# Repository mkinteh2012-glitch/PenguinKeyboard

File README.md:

# PenguinKeyboard
This is a 84 key keyboard built by @penguinmo   
Extra features on this keyboard are none! there isn't any :)  
I built this because i liked making a macropad and it's the samething as a keyboard!

## PICTURES

NOTE: for the Keyboard there is no source CAD because it is exported from kicad

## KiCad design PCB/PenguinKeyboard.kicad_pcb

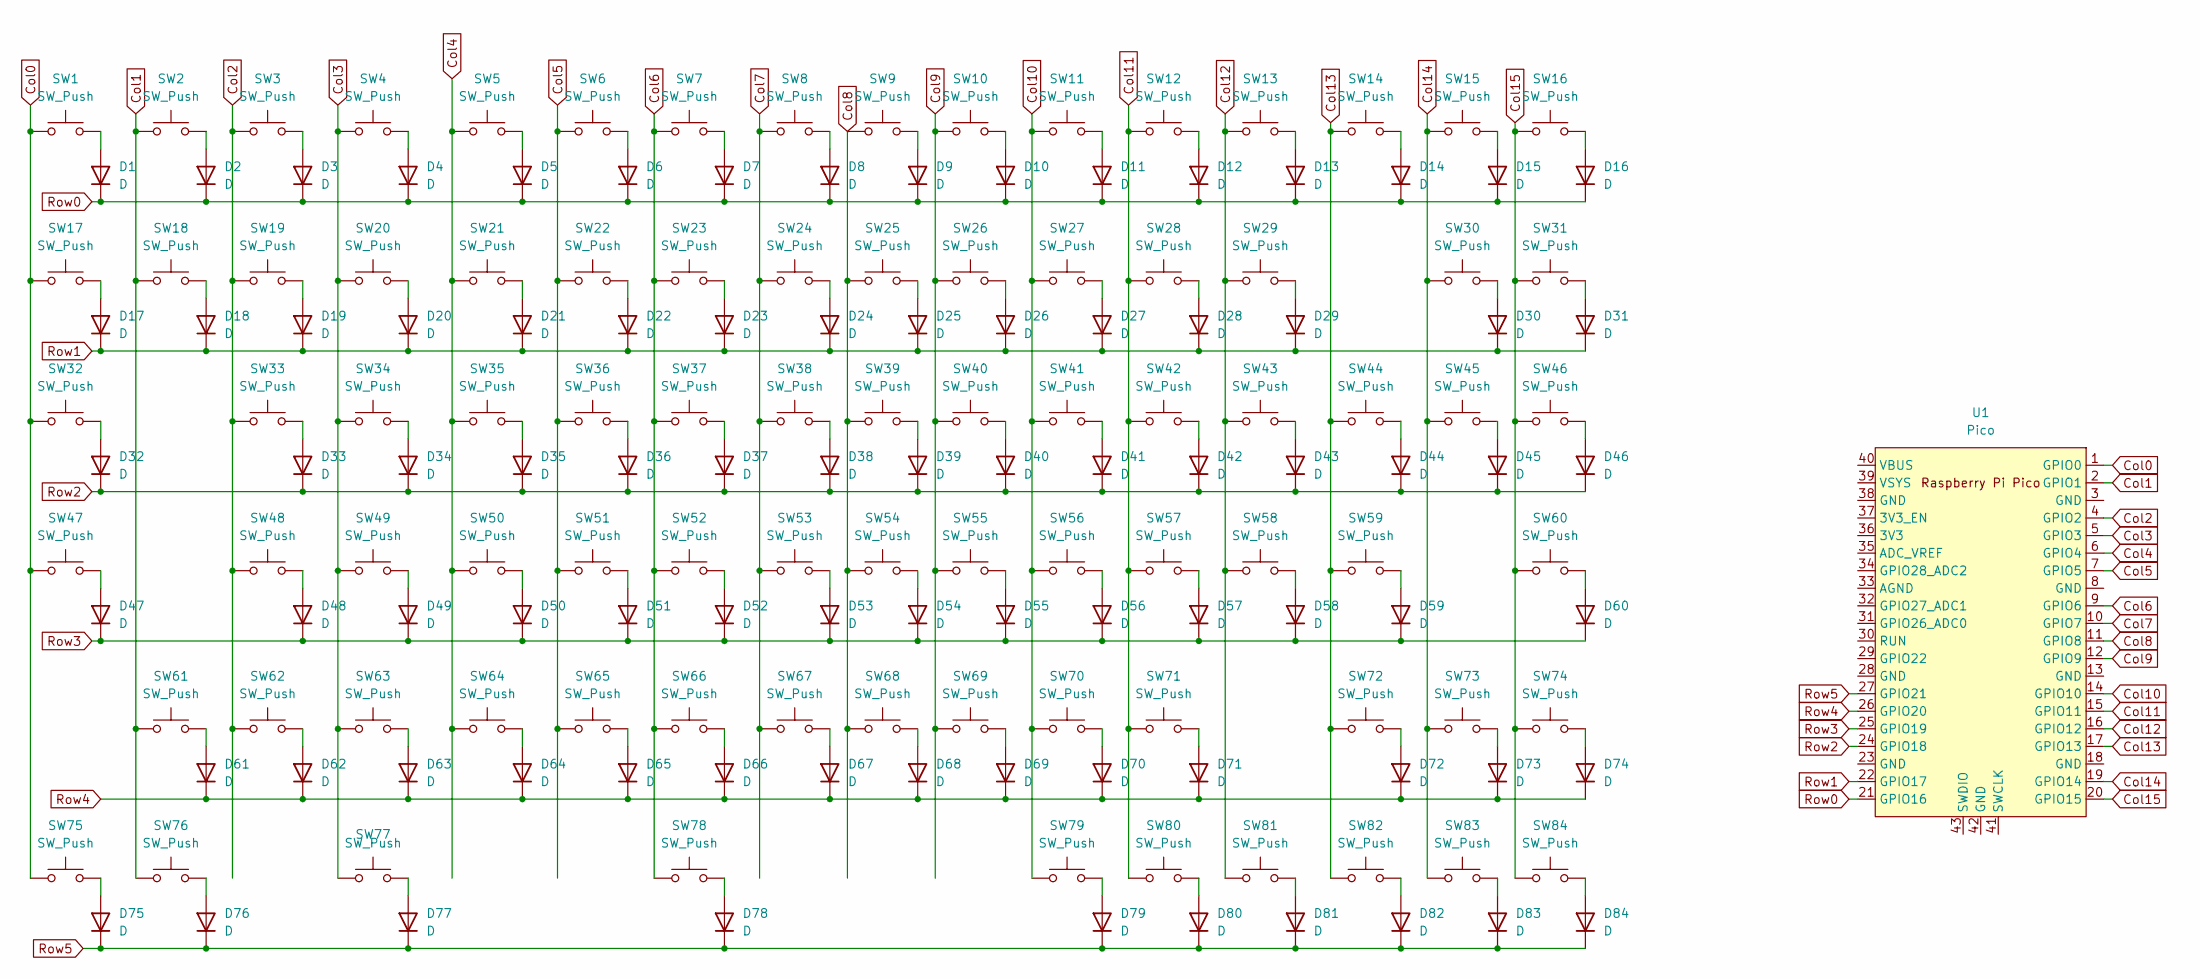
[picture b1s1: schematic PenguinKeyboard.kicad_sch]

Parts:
D1, D2, D3, D4, D5, D6, D7, D8, D9, D10, D11, D12, D13, D14, D15, D16, D17, D18, D19, D20, D21, D22, D23, D24, D25, D26, D27, D28, D29, D30, D31, D32, D33, D34, D35, D36, D37, D38, D39, D40, D41, D42, D43, D44, D45, D46, D47, D48, D49, D50, D51, D52, D53, D54, D55, D56, D57, D58, D59, D60, D61, D62, D63, D64, D65, D66, D67, D68, D69, D70, D71, D72, D73, D74, D75, D76, D77, D78, D79, D80, D81, D82, D83, D84: D; D_DO-35_SOD27_P7.62mm_Horizontal
SW1, SW2, SW3, SW4, SW5, SW6, SW7, SW8, SW9, SW10, SW11, SW12, SW13, SW14, SW15, SW16, SW17, SW18, SW19, SW20, SW21, SW22, SW23, SW24, SW25, SW26, SW27, SW28, SW29, SW30, SW31, SW32, SW33, SW34, SW35, SW36, SW37, SW38, SW39, SW40, SW41, SW42, SW43, SW44, SW45, SW46, SW47, SW48, SW49, SW50, SW51, SW52, SW53, SW54, SW55, SW56, SW57, SW58, SW59, SW60, SW61, SW62, SW63, SW64, SW65, SW66, SW67, SW68, SW69, SW70, SW71, SW72, SW73, SW74, SW75, SW76, SW77, SW78, SW79, SW80, SW81, SW82, SW83, SW84: SW_Push; SW_Cherry_MX_1.00u_PCB
U1: Pico; RPi_Pico_SMD_TH

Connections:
Col0: SW1.1, SW17.1, SW32.1, SW47.1, SW75.1, U1.1 (GPIO0)
Col1: SW2.1, SW18.1, SW61.1, SW76.1, U1.2 (GPIO1)
Col2: SW3.1, SW19.1, SW33.1, SW48.1, SW62.1, U1.4 (GPIO2)
Col3: SW4.1, SW20.1, SW34.1, SW49.1, SW63.1, SW77.1, U1.5 (GPIO3)
Col4: SW5.1, SW21.1, SW35.1, SW50.1, SW64.1, U1.6 (GPIO4)
Col5: SW6.1, SW22.1, SW36.1, SW51.1, SW65.1, U1.7 (GPIO5)
Col6: SW7.1, SW23.1, SW37.1, SW52.1, SW66.1, SW78.1, U1.9 (GPIO6)
Col7: SW8.1, SW24.1, SW38.1, SW53.1, SW67.1, U1.10 (GPIO7)
Col8: SW9.1, SW25.1, SW39.1, SW54.1, SW68.1, U1.11 (GPIO8)
Col9: SW10.1, SW26.1, SW40.1, SW55.1, SW69.1, U1.12 (GPIO9)
Col10: SW11.1, SW27.1, SW41.1, SW56.1, SW70.1, SW79.1, U1.14 (GPIO10)
Col11: SW12.1, SW28.1, SW42.1, SW57.1, SW71.1, SW80.1, U1.15 (GPIO11)
Col12: SW13.1, SW29.1, SW43.1, SW58.1, SW81.1, U1.16 (GPIO12)
Col13: SW14.1, SW44.1, SW59.1, SW72.1, SW82.1, U1.17 (GPIO13)
Col14: SW15.1, SW30.1, SW45.1, SW73.1, SW83.1, U1.19 (GPIO14)
Col15: SW16.1, SW31.1, SW46.1, SW60.1, SW74.1, SW84.1, U1.20 (GPIO15)
unnamed: D1.2 (A), SW1.2
unnamed: D2.2 (A), SW2.2
unnamed: D3.2 (A), SW3.2
unnamed: D4.2 (A), SW4.2
unnamed: D5.2 (A), SW5.2
unnamed: D6.2 (A), SW6.2
unnamed: D7.2 (A), SW7.2
unnamed: D8.2 (A), SW8.2
unnamed: D9.2 (A), SW9.2
unnamed: D10.2 (A), SW10.2
unnamed: D11.2 (A), SW11.2
unnamed: D12.2 (A), SW12.2
unnamed: D13.2 (A), SW13.2
unnamed: D14.2 (A), SW14.2
unnamed: D15.2 (A), SW15.2
unnamed: D16.2 (A), SW16.2
unnamed: D17.2 (A), SW17.2
unnamed: D18.2 (A), SW18.2
unnamed: D19.2 (A), SW19.2
unnamed: D20.2 (A), SW20.2
unnamed: D21.2 (A), SW21.2
unnamed: D22.2 (A), SW22.2
unnamed: D23.2 (A), SW23.2
unnamed: D24.2 (A), SW24.2
unnamed: D25.2 (A), SW25.2
unnamed: D26.2 (A), SW26.2
unnamed: D27.2 (A), SW27.2
unnamed: D28.2 (A), SW28.2
unnamed: D29.2 (A), SW29.2
unnamed: D30.2 (A), SW30.2
unnamed: D31.2 (A), SW31.2
unnamed: D32.2 (A), SW32.2
unnamed: D33.2 (A), SW33.2
unnamed: D34.2 (A), SW34.2
unnamed: D35.2 (A), SW35.2
unnamed: D36.2 (A), SW36.2
unnamed: D37.2 (A), SW37.2
unnamed: D38.2 (A), SW38.2
unnamed: D39.2 (A), SW39.2
unnamed: D40.2 (A), SW40.2
unnamed: D41.2 (A), SW41.2
unnamed: D42.2 (A), SW42.2
unnamed: D43.2 (A), SW43.2
unnamed: D44.2 (A), SW44.2
unnamed: D45.2 (A), SW45.2
unnamed: D46.2 (A), SW46.2
unnamed: D47.2 (A), SW47.2
unnamed: D48.2 (A), SW48.2
unnamed: D49.2 (A), SW49.2
unnamed: D50.2 (A), SW50.2
unnamed: D51.2 (A), SW51.2
unnamed: D52.2 (A), SW52.2
unnamed: D53.2 (A), SW53.2
unnamed: D54.2 (A), SW54.2
unnamed: D55.2 (A), SW55.2
unnamed: D56.2 (A), SW56.2
unnamed: D57.2 (A), SW57.2
unnamed: D58.2 (A), SW58.2
unnamed: D59.2 (A), SW59.2
unnamed: D60.2 (A), SW60.2
unnamed: D61.2 (A), SW61.2
unnamed: D62.2 (A), SW62.2
unnamed: D63.2 (A), SW63.2
unnamed: D64.2 (A), SW64.2
unnamed: D65.2 (A), SW65.2
unnamed: D66.2 (A), SW66.2
unnamed: D67.2 (A), SW67.2
unnamed: D68.2 (A), SW68.2
unnamed: D69.2 (A), SW69.2
unnamed: D70.2 (A), SW70.2
unnamed: D71.2 (A), SW71.2
unnamed: D72.2 (A), SW72.2
unnamed: D73.2 (A), SW73.2
unnamed: D74.2 (A), SW74.2
unnamed: D75.2 (A), SW75.2
unnamed: D76.2 (A), SW76.2
unnamed: D77.2 (A), SW77.2
unnamed: D78.2 (A), SW78.2
unnamed: D79.2 (A), SW79.2
unnamed: D80.2 (A), SW80.2
unnamed: D81.2 (A), SW81.2
unnamed: D82.2 (A), SW82.2
unnamed: D83.2 (A), SW83.2
unnamed: D84.2 (A), SW84.2
Row0: D1.1 (K), D2.1 (K), D3.1 (K), D4.1 (K), D5.1 (K), D6.1 (K), D7.1 (K), D8.1 (K), D9.1 (K), D10.1 (K), D11.1 (K), D12.1 (K), D13.1 (K), D14.1 (K), D15.1 (K), D16.1 (K), U1.21 (GPIO16)
Row1: D17.1 (K), D18.1 (K), D19.1 (K), D20.1 (K), D21.1 (K), D22.1 (K), D23.1 (K), D24.1 (K), D25.1 (K), D26.1 (K), D27.1 (K), D28.1 (K), D29.1 (K), D30.1 (K), D31.1 (K), U1.22 (GPIO17)
Row2: D32.1 (K), D33.1 (K), D34.1 (K), D35.1 (K), D36.1 (K), D37.1 (K), D38.1 (K), D39.1 (K), D40.1 (K), D41.1 (K), D42.1 (K), D43.1 (K), D44.1 (K), D45.1 (K), D46.1 (K), U1.24 (GPIO18)
Row3: D47.1 (K), D48.1 (K), D49.1 (K), D50.1 (K), D51.1 (K), D52.1 (K), D53.1 (K), D54.1 (K), D55.1 (K), D56.1 (K), D57.1 (K), D58.1 (K), D59.1 (K), D60.1 (K), U1.25 (GPIO19)
Row4: D61.1 (K), D62.1 (K), D63.1 (K), D64.1 (K), D65.1 (K), D66.1 (K), D67.1 (K), D68.1 (K), D69.1 (K), D70.1 (K), D71.1 (K), D72.1 (K), D73.1 (K), D74.1 (K), U1.26 (GPIO20)
Row5: D75.1 (K), D76.1 (K), D77.1 (K), D78.1 (K), D79.1 (K), D80.1 (K), D81.1 (K), D82.1 (K), D83.1 (K), D84.1 (K), U1.27 (GPIO21)

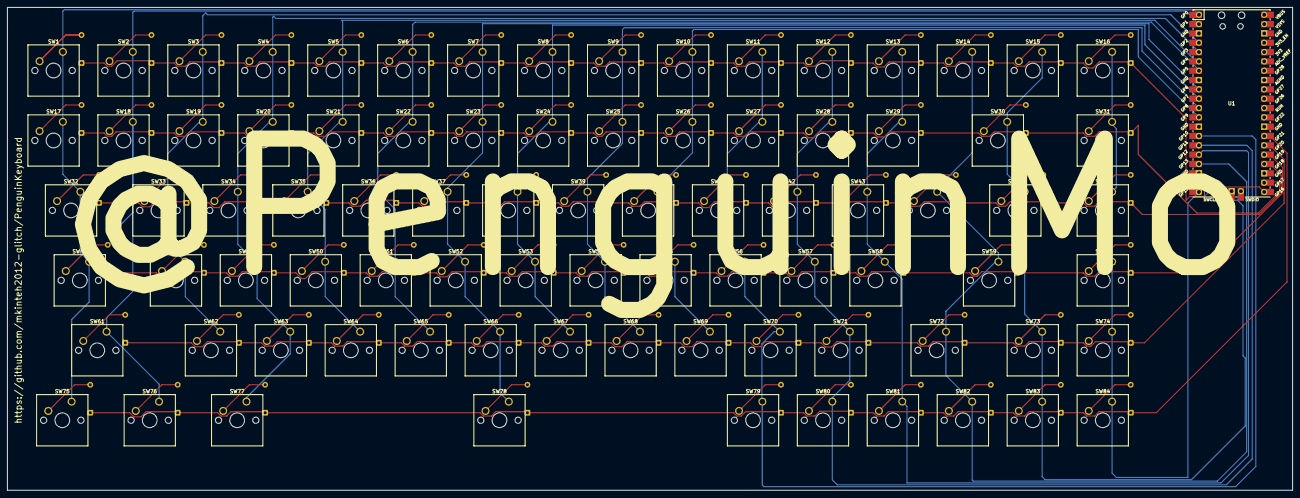
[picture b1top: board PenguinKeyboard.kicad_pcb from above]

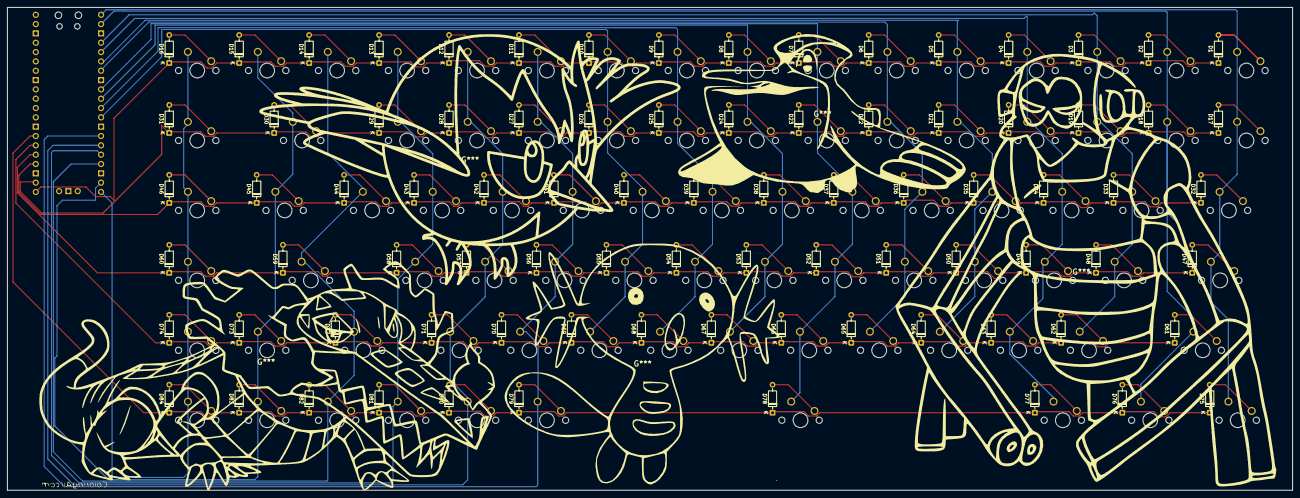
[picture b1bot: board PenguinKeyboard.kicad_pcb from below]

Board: 2 copper layers, 350.0 x 131.5 mm, 169 parts (84 on the bottom side), 106 nets.

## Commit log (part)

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2026-01-04 Rename PenguinKeyboard.kicad_pro to PCB/PenguinKeyboard.kicad_pro
2026-01-04 Rename PRODUCTION.zip to PRODUCTION/PRODUCTION.zip
2026-01-04 Enhance README with additional sections
    Added sections for Pictures, Schematic, and PCB to README.
2026-01-13 Enhance README with keyboard details and images
    Added additional sections and images to README.
2026-01-13 Fix typo in README and add smiley face
2026-01-13 Remove an image from the README
2026-05-02 Rename PenguinKeyboard.step to CAD/KeyboardPCB.step
2026-05-02 Add note regarding keyboard CAD source
    Added note about the absence of source CAD for the keyboard.
2026-05-02 Refactor keyboard setup and keymap configuration
2026-05-03 Rename PicoBoard BOM - Sheet1.csv to PicoBoard BOM.csv
2026-05-03 Rename PicoBoard BOM.csv to BOM.csv
2026-05-03 Add more images to README
    Added additional images to the README for better visualization.
